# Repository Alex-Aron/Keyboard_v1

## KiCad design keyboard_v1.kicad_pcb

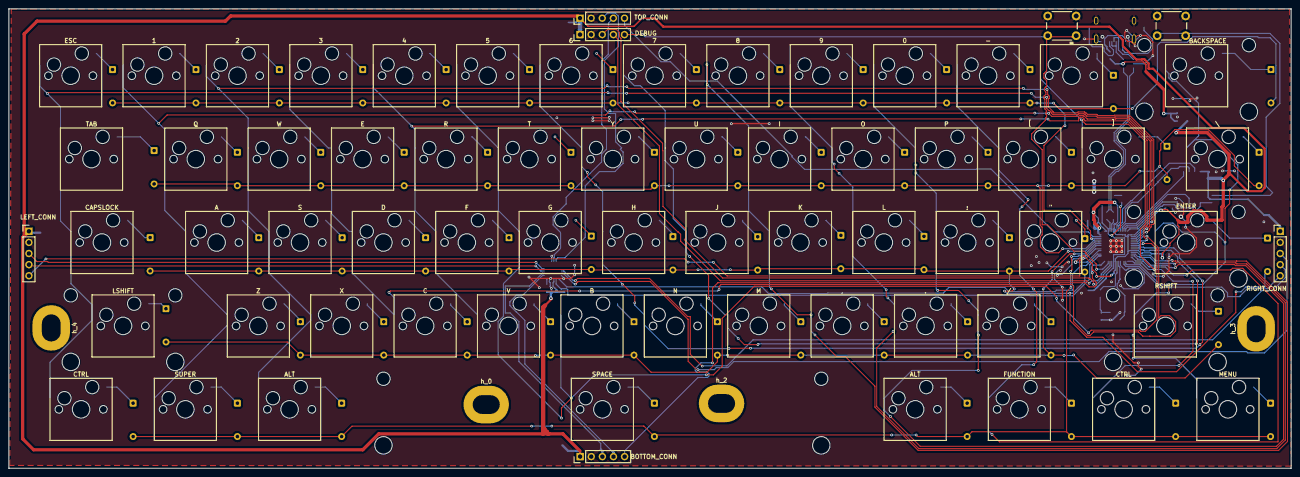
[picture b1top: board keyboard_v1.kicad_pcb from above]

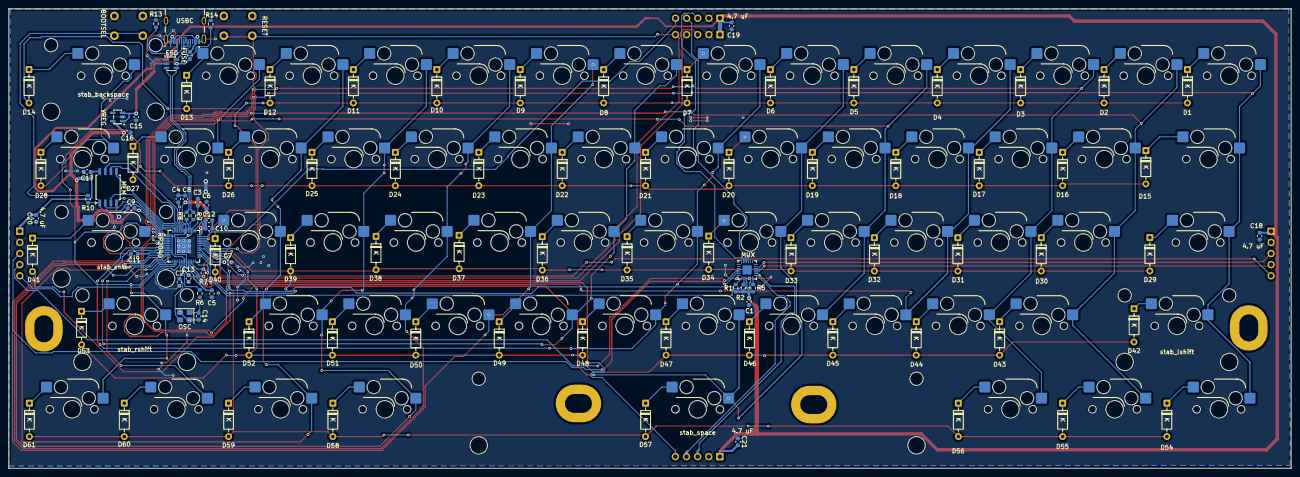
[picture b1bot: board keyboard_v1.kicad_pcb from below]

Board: 2 copper layers, 292.9 x 104.9 mm, 177 parts (100 on the bottom side), 121 nets.

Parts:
0, 2, 3, 4, 5, 6, 7, 8, 9, .: Keyswitch; SW_Hotswap_Kailh_MX_1.00u
1: SW_Push; SW_Hotswap_Kailh_MX_1.00u
": Keyswitch; SW_Hotswap_Kailh_MX_1.00u
,: Keyswitch; SW_Hotswap_Kailh_MX_1.00u
-: Keyswitch; SW_Hotswap_Kailh_MX_1.00u
/: Keyswitch; SW_Hotswap_Kailh_MX_1.00u
:: Keyswitch; SW_Hotswap_Kailh_MX_1.00u
=: Keyswitch; SW_Hotswap_Kailh_MX_1.00u
A: Keyswitch; SW_Hotswap_Kailh_MX_1.00u
ALT: Keyswitch; SW_Hotswap_Kailh_MX_1.25u
ALT#2: Keyswitch; SW_Hotswap_Kailh_MX_1.25u
B: Keyswitch; SW_Hotswap_Kailh_MX_1.00u
BACKSPACE: Keyswitch; SW_Hotswap_Kailh_MX_2.00u
BOOTSEL: BOOTSEL; SW_PUSH_6mm
BOTTOM_CONN: Conn_Bottom; PinHeader_1x05_P2.54mm_Vertical
C: Keyswitch; SW_Hotswap_Kailh_MX_1.00u
C1, C17: 100 nF; C_0603_1608Metric
C2, C14: 15pF; C_0603_1608Metric
C3: 1uF; C_0603_1608Metric
C4, C5: 100nF; C_0603_1608Metric
C6, C15, C16: 1 uF; C_0603_1608Metric
C7, C8, C9, C10, C11, C12, C13: 100n; C_0603_1608Metric
C18, C19, C20, C21: 4.7 uF; C_0603_1608Metric
CAPSLOCK: Keyswitch; SW_Hotswap_Kailh_MX_1.75u
CTRL: Keyswitch; SW_Hotswap_Kailh_MX_1.25u
CTRL#2: Keyswitch; SW_Hotswap_Kailh_MX_1.25u
D: Keyswitch; SW_Hotswap_Kailh_MX_1.00u
D1, D2, D3, D4, D5, D6, D7, D8, D9, D10, D11, D12, D13, D14, D15, D16, D17, D18, D19, D20, D21, D22, D23, D24, D25, D26, D27, D28, D29, D30, D31, D32, D33, D34, D35, D36, D37, D38, D39, D40, D41, D42, D43, D44, D45, D46, D47, D48, D49, D50, D51, D52, D53, D54, D55, D56, D57, D58, D59, D60, D61: Diode; D_DO-35_SOD27_P7.62mm_Horizontal
DEBUG: Conn_Debug; PinHeader_1x05_P2.54mm_Vertical
E: Keyswitch; SW_Hotswap_Kailh_MX_1.00u
ENTER: Keyswitch; SW_Hotswap_Kailh_MX_2.25u
ESC: Keyswitch; SW_Hotswap_Kailh_MX_1.00u
ESD: USBLC6-2SC6; SOT-23-6
F: Keyswitch; SW_Hotswap_Kailh_MX_1.00u
FUNCTION: Keyswitch; SW_Hotswap_Kailh_MX_1.25u
FUSE: 500 mA; Fuse_0603_1608Metric
G: Keyswitch; SW_Hotswap_Kailh_MX_1.00u
H: Keyswitch; SW_Hotswap_Kailh_MX_1.00u
I: Keyswitch; SW_Hotswap_Kailh_MX_1.00u
J: Keyswitch; SW_Hotswap_Kailh_MX_1.00u
K: Keyswitch; SW_Hotswap_Kailh_MX_1.00u
L: Keyswitch; SW_Hotswap_Kailh_MX_1.00u
LEFT_CONN: Conn_Left; PinHeader_1x05_P2.54mm_Vertical
LSHIFT: Keyswitch; SW_Hotswap_Kailh_MX_2.25u
M: Keyswitch; SW_Hotswap_Kailh_MX_1.00u
MEM: W25Q128JVS; SOIC-8_5.3x5.3mm_P1.27mm
MENU: Keyswitch; SW_Hotswap_Kailh_MX_1.25u
MUX: TCA9548AMRGER; Texas_RGE0024C_VQFN-24-1EP_4x4mm_P0.5mm_EP2.1x2.1mm
N: Keyswitch; SW_Hotswap_Kailh_MX_1.00u
O: Keyswitch; SW_Hotswap_Kailh_MX_1.00u
OSC: Crystal_GND24; Crystal_SMD_3225-4Pin_3.2x2.5mm
P: Keyswitch; SW_Hotswap_Kailh_MX_1.00u
Q: Keyswitch; SW_Hotswap_Kailh_MX_1.00u
R: Keyswitch; SW_Hotswap_Kailh_MX_1.00u
R1, R2: 10k; R_0603_1608Metric
R5: 4.7k; R_0603_1608Metric
R6, R7, R10: 1k; R_0603_1608Metric
R8, R9: 27.4; R_0603_1608Metric
R13, R14: 5k; R_0603_1608Metric
RESET: RESET; SW_PUSH_6mm
RIGHT_CONN: Conn_Right; PinHeader_1x05_P2.54mm_Vertical
RP2040: RP2040; QFN-56-1EP_7x7mm_P0.4mm_EP3.2x3.2mm
RSHIFT: Keyswitch; SW_Hotswap_Kailh_MX_2.75u
S: Keyswitch; SW_Hotswap_Kailh_MX_1.00u
SPACE: Keyswitch; SW_Hotswap_Kailh_MX_6.25u
SUPER: Keyswitch; SW_Hotswap_Kailh_MX_1.25u
T: Keyswitch; SW_Hotswap_Kailh_MX_1.00u
TAB: Keyswitch; SW_Hotswap_Kailh_MX_1.50u
TOP_CONN: Conn_Top; PinHeader_1x05_P2.54mm_Vertical
U: Keyswitch; SW_Hotswap_Kailh_MX_1.00u
USBC: USB4105-GF-A; GCT_USB4105-GF-A
V: Keyswitch; SW_Hotswap_Kailh_MX_1.00u
VREG: AP2112K-3.3; SOT-23-5
W: Keyswitch; SW_Hotswap_Kailh_MX_1.00u
X: Keyswitch; SW_Hotswap_Kailh_MX_1.00u
Y: Keyswitch; SW_Hotswap_Kailh_MX_1.00u
Z: Keyswitch; SW_Hotswap_Kailh_MX_1.00u
[: Keyswitch; SW_Hotswap_Kailh_MX_1.00u
\: Keyswitch; SW_Hotswap_Kailh_MX_1.50u
]: Keyswitch; SW_Hotswap_Kailh_MX_1.00u
h_0, h_3, h_4: H1; MountingHole_4.3x6.2mm_M4_Pad
h_2: H2; MountingHole_4.3x6.2mm_M4_Pad
stab_backspace: Stabilizer_Cherry_MX_2.00u
stab_enter: Stabilizer_Cherry_MX_2.00u
stab_lshift: Stabilizer_Cherry_MX_2.00u
stab_rshift: Stabilizer_Cherry_MX_2.00u
stab_space: Stabilizer_Cherry_MX_6.25u

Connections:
+1V1: C3.1, C4.1, C5.1, RP2040.23 (DVDD), RP2040.45 (VREG_VOUT), RP2040.50 (DVDD)
+3V3: BOTTOM_CONN.1, C1.1, C6.1, C7.1, C8.1, C9.1, C10.1, C11.1, C12.1, C13.1, C16.1, C17.1, C18.2, C19.2, C20.2, C21.2, DEBUG.1, LEFT_CONN.1, MEM.8 (VCC), MUX.21 (VCC), R1.1, R2.1, R5.2, R7.1, RIGHT_CONN.1, RP2040.1 (IOVDD), RP2040.10 (IOVDD), RP2040.22 (IOVDD), RP2040.33 (IOVDD), RP2040.42 (IOVDD), RP2040.43 (ADC_AVDD), RP2040.44 (VREG_IN), RP2040.48 (USB_VDD), RP2040.49 (IOVDD), TOP_CONN.1, VREG.5 (VOUT)
+5V: C15.1, ESD.5 (VBUS), FUSE.2, VREG.1 (VIN), VREG.3 (EN)
CS: MEM.1 (~CS), R10.2, RP2040.56 (QSPI_SS)
Col 0: CAPSLOCK.1, CTRL.1, ESC.1, LSHIFT.1, RP2040.2 (GPIO0), TAB.1
Col 1: 1.1, A.1, Q.1, RP2040.3 (GPIO1), SUPER.1, Z.1
Col 2: 2.1, ALT.1, RP2040.4 (GPIO2), S.1, W.1, X.1
Col 3: 3.1, C.1, D.1, E.1, RP2040.5 (GPIO3)
Col 4: 4.1, F.1, R.1, RP2040.6 (GPIO4), V.1
Col 5: 5.1, B.1, G.1, RP2040.7 (GPIO5), SPACE.1, T.1
Col 6: 6.1, H.1, N.1, RP2040.8 (GPIO6), Y.1
Col 7: 7.1, J.1, M.1, RP2040.9 (GPIO7), U.1
Col 8: 8.1, ,.1, I.1, K.1, RP2040.11 (GPIO8)
Col 9: 9.1, ..1, L.1, O.1, RP2040.12 (GPIO9)
Col 10: 0.1, /.1, :.1, ALT#2.1, P.1, RP2040.13 (GPIO10)
Col 11: ".1, -.1, FUNCTION.1, RP2040.14 (GPIO11), [.1
Col 12: =.1, CTRL#2.1, RP2040.15 (GPIO12), ].1
Col 13: BACKSPACE.1, ENTER.1, MENU.1, RP2040.16 (GPIO13), RSHIFT.1, \.1
D_N: ESD.4 (I/O2), R9.2
D_P: ESD.3 (I/O2), R8.2
D_USB_N: ESD.6 (I/O1), USBC.A7 (DN1), USBC.B7 (DN2)
D_USB_P: ESD.1 (I/O1), USBC.A6 (DP1), USBC.B6 (DP2)
GND: BOOTSEL.1, BOTTOM_CONN.2, C1.2, C2.1, C3.2, C4.2, C5.2, C6.2, C7.2, C8.2, C9.2, C10.2, C11.2, C12.2, C13.2, C14.1, C15.2, C16.2, C17.2, C18.1, C19.1, C20.1, C21.1, DEBUG.2, ESD.2 (GND), LEFT_CONN.2, MEM.4 (GND), MUX.9 (GND), MUX.18 (A2), MUX.22 (A0), MUX.23 (A1), OSC.2, OSC.4, R13.2, R14.2, RESET.2, RIGHT_CONN.2, RP2040.19 (TESTEN), RP2040.57 (GND), TOP_CONN.2, USBC.A1_B12 (GND), USBC.B1_A12 (GND), USBC.SH1 (SHELL_GND), USBC.SH2 (SHELL_GND), USBC.SH3 (SHELL_GND), USBC.SH4 (SHELL_GND), VREG.2 (GND)
INT_BOTTOM: BOTTOM_CONN.5, RP2040.28 (GPIO17)
INT_LEFT: LEFT_CONN.5, RP2040.34 (GPIO22)
INT_RIGHT: RIGHT_CONN.5, RP2040.17 (GPIO14)
INT_TOP: RP2040.41 (GPIO29_ADC3), TOP_CONN.5
unnamed: C14.2, OSC.1, R6.1
unnamed: D1.1 (K), ESC.2
unnamed: 1.2, D2.1 (K)
unnamed: 2.2, D3.1 (K)
unnamed: 3.2, D4.1 (K)
unnamed: 4.2, D5.1 (K)
unnamed: 5.2, D6.1 (K)
unnamed: 6.2, D7.1 (K)
unnamed: 7.2, D8.1 (K)
unnamed: 8.2, D9.1 (K)
unnamed: 9.2, D10.1 (K)
unnamed: 0.2, D11.1 (K)
unnamed: -.2, D12.1 (K)
unnamed: =.2, D13.1 (K)
unnamed: BACKSPACE.2, D14.1 (K)
unnamed: D15.1 (K), TAB.2
unnamed: D16.1 (K), Q.2
unnamed: D17.1 (K), W.2
unnamed: D18.1 (K), E.2
unnamed: D19.1 (K), R.2
unnamed: D20.1 (K), T.2
unnamed: D21.1 (K), Y.2
unnamed: D22.1 (K), U.2
unnamed: D23.1 (K), I.2
unnamed: D24.1 (K), O.2
unnamed: D25.1 (K), P.2
unnamed: D26.1 (K), [.2
unnamed: D27.1 (K), ].2
unnamed: D28.1 (K), \.2
unnamed: CAPSLOCK.2, D29.1 (K)
unnamed: A.2, D30.1 (K)
unnamed: D31.1 (K), S.2
unnamed: D.2, D32.1 (K)
unnamed: D33.1 (K), F.2
unnamed: D34.1 (K), G.2
unnamed: D35.1 (K), H.2
unnamed: D36.1 (K), J.2
unnamed: D37.1 (K), K.2
unnamed: D38.1 (K), L.2
unnamed: :.2, D39.1 (K)
unnamed: ".2, D40.1 (K)
unnamed: D41.1 (K), ENTER.2
unnamed: D42.1 (K), LSHIFT.2
unnamed: D43.1 (K), Z.2
unnamed: D44.1 (K), X.2
unnamed: C.2, D45.1 (K)
unnamed: D46.1 (K), V.2
unnamed: B.2, D47.1 (K)
unnamed: D48.1 (K), N.2
unnamed: D49.1 (K), M.2
unnamed: ,.2, D50.1 (K)
unnamed: ..2, D51.1 (K)
unnamed: /.2, D52.1 (K)
unnamed: D53.1 (K), RSHIFT.2
unnamed: CTRL.2, D54.1 (K)
unnamed: D55.1 (K), SUPER.2
unnamed: ALT.2, D56.1 (K)
unnamed: D57.1 (K), SPACE.2
unnamed: ALT#2.2, D58.1 (K)
unnamed: D59.1 (K), FUNCTION.2
unnamed: CTRL#2.2, D60.1 (K)
unnamed: D61.1 (K), MENU.2
unnamed: R14.1, USBC.A5 (CC1)
unnamed: R13.1, USBC.B5 (CC2)
unnamed: BOOTSEL.2, R10.1
unnamed: MUX.24 (~RESET), R5.1
unnamed: R9.1, RP2040.46 (USB_DM)
unnamed: R8.1, RP2040.47 (USB_DP)
QSPI_CLK: MEM.6 (CLK), RP2040.52 (QSPI_SCLK)
RESET: DEBUG.5, R7.2, RESET.1, RP2040.26 (RUN)
Row 0: D1.2 (A), D2.2 (A), D3.2 (A), D4.2 (A), D5.2 (A), D6.2 (A), D7.2 (A), D8.2 (A), D9.2 (A), D10.2 (A), D11.2 (A), D12.2 (A), D13.2 (A), D14.2 (A), RP2040.40 (GPIO28_ADC2)
Row 1: D15.2 (A), D16.2 (A), D17.2 (A), D18.2 (A), D19.2 (A), D20.2 (A), D21.2 (A), D22.2 (A), D23.2 (A), D24.2 (A), D25.2 (A), D26.2 (A), D27.2 (A), D28.2 (A), RP2040.39 (GPIO27_ADC1)
Row 2: D29.2 (A), D30.2 (A), D31.2 (A), D32.2 (A), D33.2 (A), D34.2 (A), D35.2 (A), D36.2 (A), D37.2 (A), D38.2 (A), D39.2 (A), D40.2 (A), D41.2 (A), RP2040.38 (GPIO26_ADC0)
Row 3: D42.2 (A), D43.2 (A), D44.2 (A), D45.2 (A), D46.2 (A), D47.2 (A), D48.2 (A), D49.2 (A), D50.2 (A), D51.2 (A), D52.2 (A), D53.2 (A), RP2040.37 (GPIO25)
Row 4: D54.2 (A), D55.2 (A), D56.2 (A), D57.2 (A), D58.2 (A), D59.2 (A), D60.2 (A), D61.2 (A), RP2040.36 (GPIO24)
SCL: MUX.19 (SCL), R1.2, RP2040.31 (GPIO20)
SCL_BOTTOM: BOTTOM_CONN.3, MUX.2 (SC0)
SCL_LEFT: LEFT_CONN.3, MUX.4 (SC1)
SCL_RIGHT: MUX.17 (SC7), RIGHT_CONN.3
SCL_TOP: MUX.11 (SC4), TOP_CONN.3
SD0: MEM.5 (DI/IO_{0}), RP2040.53 (QSPI_SD0)
SD1: MEM.2 (DO/IO_{1}), RP2040.55 (QSPI_SD1)
SD2: MEM.3 (~WP/IO_{2}), RP2040.54 (QSPI_SD2)
SD3: MEM.7 (~HOLD/~RESET/IO_{3}), RP2040.51 (QSPI_SD3)
SDA: MUX.20 (SDA), R2.2, RP2040.30 (GPIO19)
SDA_BOTTOM: BOTTOM_CONN.4, MUX.1 (SD0)
SDA_LEFT: LEFT_CONN.4, MUX.3 (SD1)
SDA_RIGHT: MUX.16 (SD7), RIGHT_CONN.4
SDA_TOP: MUX.10 (SD4), TOP_CONN.4
SWCLK: DEBUG.3, RP2040.24 (SWCLK)
SWD: DEBUG.4, RP2040.25 (SWD)
VBUS: FUSE.1, USBC.A4_B9 (VBUS), USBC.B4_A9 (VBUS)
XIN: C2.2, OSC.3, RP2040.20 (XIN)
XOUT: R6.2, RP2040.21 (XOUT)

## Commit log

2026-02-17 Upload just base board
